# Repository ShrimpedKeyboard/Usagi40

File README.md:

# Usagi40
## a 40% ortholinear keyboard

The Usagi40 is an ortholinear 40% keyboard with two blockers to the left and right of the 7u Spacebar
also has a strap

 --- 

## Case

usagi uses a 7 layer stacked acrylic case with a sandwhich mount case
The case uses m3 spacers and screws

 --- 

## PCB

A hotswap pro micro RP2040 pcb 

 --- 

## Misc
I plan to sell this board instock in the future once my storefront is at 
this board is untested at the momment i do not recomend producing it 
DM xshrimped on discord if you have any questions
https://discord.gg/pNWCxb3Fh5

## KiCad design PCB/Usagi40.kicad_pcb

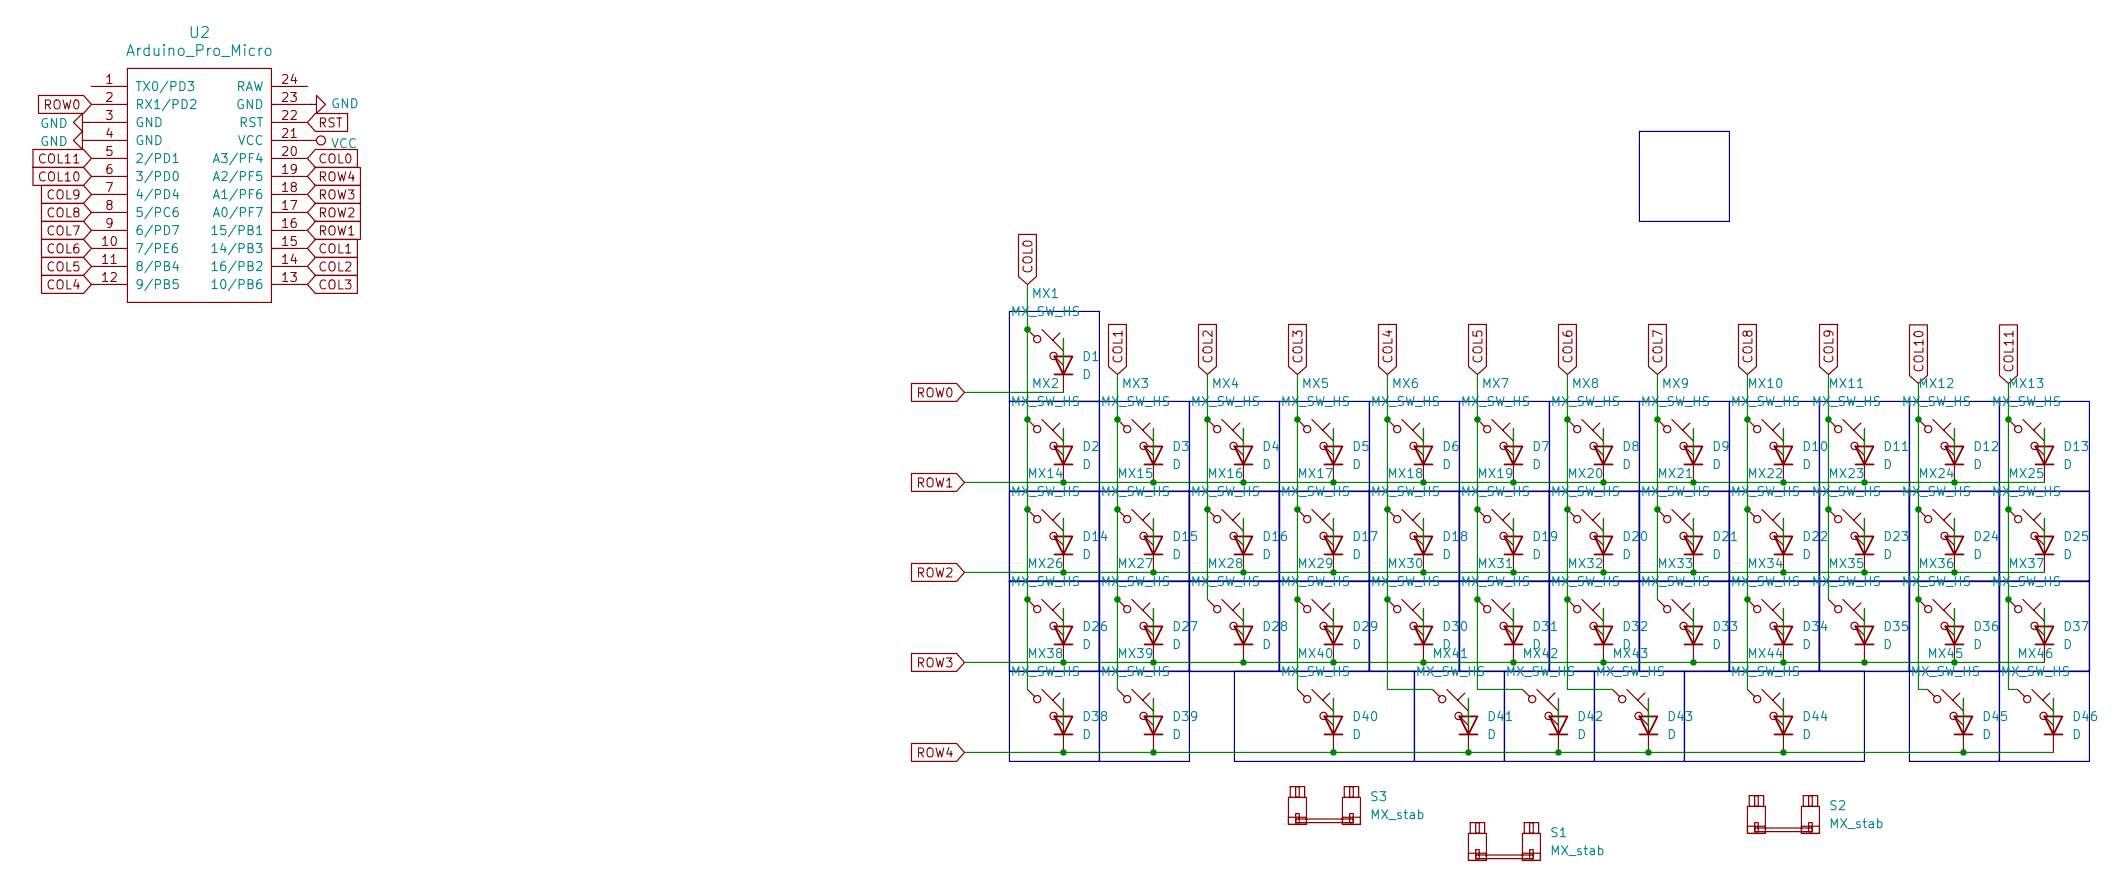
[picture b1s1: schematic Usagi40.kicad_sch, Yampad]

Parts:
D1, D2, D3, D4, D5, D6, D7, D8, D9, D10, D11, D12, D13, D14, D15, D16, D17, D18, D19, D20, D21, D22, D23, D24, D25, D26, D27, D28, D29, D30, D31, D32, D33, D34, D35, D36, D37, D38, D39, D40, D41, D42, D43, D44, D45, D46: D; D_SOD-123
MX1, MX2, MX3, MX4, MX5, MX6, MX7, MX8, MX9, MX10, MX11, MX12, MX13, MX14, MX15, MX16, MX17, MX18, MX19, MX20, MX21, MX22, MX23, MX24, MX25, MX26, MX27, MX28, MX29, MX30, MX31, MX32, MX33, MX34, MX35, MX36, MX37, MX38, MX39, MX40, MX41, MX42, MX43, MX44, MX45, MX46: MX_SW_HS; SW_MX_HS_CPG151101S11_1u
S1: MX_stab; STAB_MX_P_7u
S2, S3: MX_stab; STAB_MX_P_2u
U2: Arduino_Pro_Micro

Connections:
COL0: MX1.1, MX2.1, MX14.1, MX26.1, MX38.1, U2.20 (A3/PF4)
COL1: MX3.1, MX15.1, MX27.1, MX39.1, U2.15 (14/PB3)
COL2: MX4.1, MX16.1, MX28.1, U2.14 (16/PB2)
COL3: MX5.1, MX17.1, MX29.1, MX40.1, U2.13 (10/PB6)
COL4: MX6.1, MX18.1, MX30.1, MX41.1, U2.12 (9/PB5)
COL5: MX7.1, MX19.1, MX31.1, MX42.1, U2.11 (8/PB4)
COL6: MX8.1, MX20.1, MX32.1, MX43.1, U2.10 (7/PE6)
COL7: MX9.1, MX21.1, MX33.1, U2.9 (6/PD7)
COL8: MX10.1, MX22.1, MX34.1, MX44.1, U2.8 (5/PC6)
COL9: MX11.1, MX23.1, MX35.1, U2.7 (4/PD4)
COL10: MX12.1, MX24.1, MX36.1, MX45.1, U2.6 (3/PD0)
COL11: MX13.1, MX25.1, MX37.1, MX46.1, U2.5 (2/PD1)
GND: U2.3 (GND), U2.4 (GND), U2.23 (GND)
unnamed: D1.2 (A), MX1.2
unnamed: D2.2 (A), MX2.2
unnamed: D3.2 (A), MX3.2
unnamed: D4.2 (A), MX4.2
unnamed: D5.2 (A), MX5.2
unnamed: D6.2 (A), MX6.2
unnamed: D7.2 (A), MX7.2
unnamed: D8.2 (A), MX8.2
unnamed: D9.2 (A), MX9.2
unnamed: D10.2 (A), MX10.2
unnamed: D11.2 (A), MX11.2
unnamed: D12.2 (A), MX12.2
unnamed: D13.2 (A), MX13.2
unnamed: D14.2 (A), MX14.2
unnamed: D15.2 (A), MX15.2
unnamed: D16.2 (A), MX16.2
unnamed: D17.2 (A), MX17.2
unnamed: D18.2 (A), MX18.2
unnamed: D19.2 (A), MX19.2
unnamed: D20.2 (A), MX20.2
unnamed: D21.2 (A), MX21.2
unnamed: D22.2 (A), MX22.2
unnamed: D23.2 (A), MX23.2
unnamed: D24.2 (A), MX24.2
unnamed: D25.2 (A), MX25.2
unnamed: D26.2 (A), MX26.2
unnamed: D27.2 (A), MX27.2
unnamed: D28.2 (A), MX28.2
unnamed: D29.2 (A), MX29.2
unnamed: D30.2 (A), MX30.2
unnamed: D31.2 (A), MX31.2
unnamed: D32.2 (A), MX32.2
unnamed: D33.2 (A), MX33.2
unnamed: D34.2 (A), MX34.2
unnamed: D35.2 (A), MX35.2
unnamed: D36.2 (A), MX36.2
unnamed: D37.2 (A), MX37.2
unnamed: D38.2 (A), MX38.2
unnamed: D39.2 (A), MX39.2
unnamed: D40.2 (A), MX40.2
unnamed: D41.2 (A), MX41.2
unnamed: D42.2 (A), MX42.2
unnamed: D43.2 (A), MX43.2
unnamed: D44.2 (A), MX44.2
unnamed: D45.2 (A), MX45.2
unnamed: D46.2 (A), MX46.2
ROW0: D1.1 (K), U2.2 (RX1/PD2)
ROW1: D2.1 (K), D3.1 (K), D4.1 (K), D5.1 (K), D6.1 (K), D7.1 (K), D8.1 (K), D9.1 (K), D10.1 (K), D11.1 (K), D12.1 (K), D13.1 (K), U2.16 (15/PB1)
ROW2: D14.1 (K), D15.1 (K), D16.1 (K), D17.1 (K), D18.1 (K), D19.1 (K), D20.1 (K), D21.1 (K), D22.1 (K), D23.1 (K), D24.1 (K), D25.1 (K), U2.17 (A0/PF7)
ROW3: D26.1 (K), D27.1 (K), D28.1 (K), D29.1 (K), D30.1 (K), D31.1 (K), D32.1 (K), D33.1 (K), D34.1 (K), D35.1 (K), D36.1 (K), D37.1 (K), U2.18 (A1/PF6)
ROW4: D38.1 (K), D39.1 (K), D40.1 (K), D41.1 (K), D42.1 (K), D43.1 (K), D44.1 (K), D45.1 (K), D46.1 (K), U2.19 (A2/PF5)
RST: U2.22 (RST)
VCC: U2.21 (VCC)

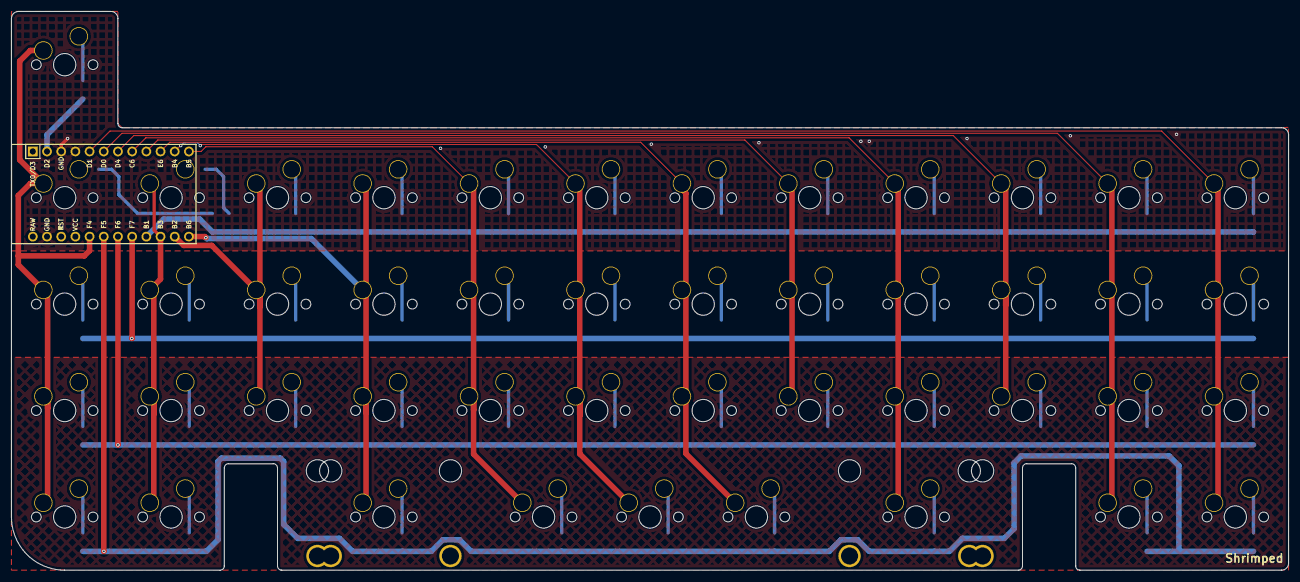
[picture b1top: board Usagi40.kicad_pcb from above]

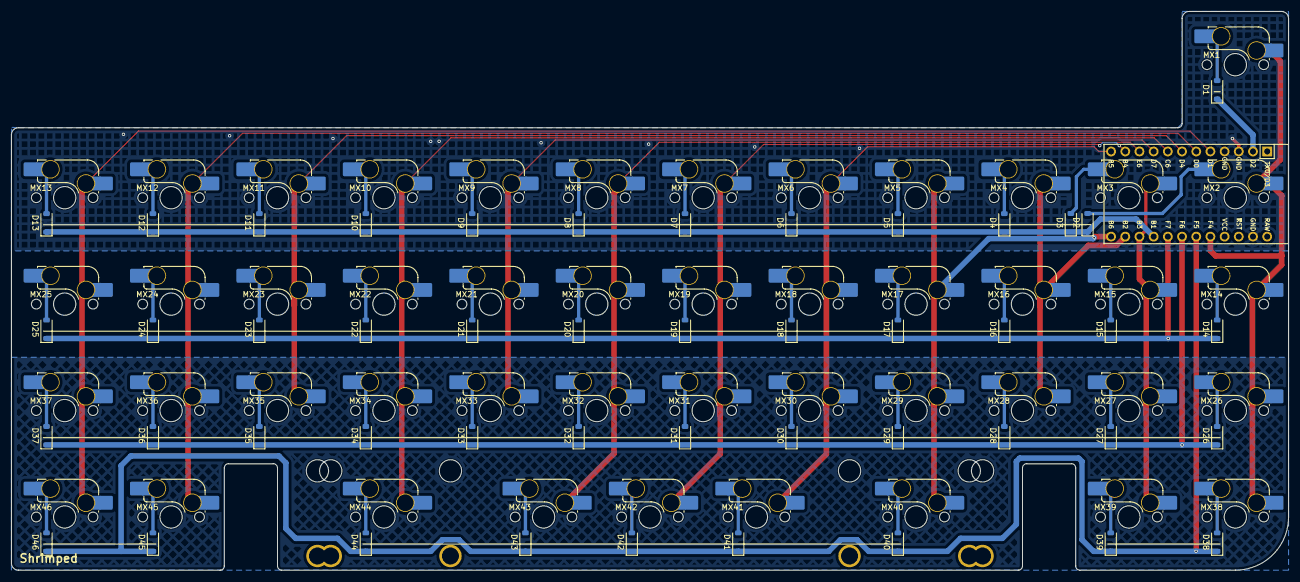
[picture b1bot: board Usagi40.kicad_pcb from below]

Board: 2 copper layers, 228.6 x 100.0 mm, 96 parts (96 on the bottom side), 64 nets.

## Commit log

2024-11-05 yeah
